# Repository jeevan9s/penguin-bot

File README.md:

# penguin

> <b>P</b>erception-<b>E</b>nabled <b>N</b>avigation and <b>G</b>eneral-<b>U</b>tility <b>IN</b>telligence

Hybrid differential legged-wheeled biped rover for embodied AI, computer vision, and autonomous navigation.

### Status

> - Controller manufactured and partially assembled.
> - Soldering and hardware validation in progress.
> - Mechanical components currently being printed.

<details>`
<summary><strong>Table of Contents</strong></summary>

- [penguin](#penguin)
    - [Status](#status)
  - [Overview](#overview)
  - [Features](#features)
    - [Controller](#controller)
    - [Mechanical](#mechanical)
  - [Architecture](#architecture)
    - [Systems](#systems)
  - [Electrical](#electrical)
    - [Power System](#power-system)
    - [Microcontroller](#microcontroller)
    - [Motor Drivers](#motor-drivers)
    - [Vision Interface](#vision-interface)
    - [Sensor and I2C Interface](#sensor-and-i2c-interface)
    - [Bugs](#bugs)
  - [Mechanical](#mechanical-1)
    - [Chassis](#chassis)
    - [Leg Assembly](#leg-assembly)
  - [Firmware](#firmware)
    - [Architecture](#architecture-1)
    - [Drivers](#drivers)
    - [Engine](#engine)
      - [State \& System Definitions](#state--system-definitions)
      - [Controllers \& Locomotion](#controllers--locomotion)
      - [Behaviour](#behaviour)
    - [Networking](#networking)
    - [GUI](#gui)
  - [Gallery](#gallery)

</details>

I built penguin cause I wanted to create an intelligent robot from the ground up.

<table>
  <tr>
    <td width="50%">
      
    </td>
    <td width="50%">
      
    </td>
  </tr>
  <tr>
    <td width="50%">
      
    </td>
    <td width="50%">
      
    </td>
  </tr>
    <tr>
    <td width="50%">
      
    </td>
    <td width="50%">
      
    </td>
  </tr>
</table>

## Overview

Put simply, Penguin is a platform for experimentation with intelligent robotics.

The project began as a simpler, maze-solving rover for a course project (MREN 178 - DSA). My team couldn't deliver the rover in time
so we scaled down. I had already started with hardware, which pushed me to adopt the project into my own, with the intent to expand it past maze-solving.

After that term (Winter '26), I designed a controller PCB and the necessary compoments for the chassis.

Now its September, and I'm tuning PID.

## Features

### Controller

The controller is powered by a 7.4V LiPo Battery and driven by an ESP32-S3 (N16 1U).

Below is a list of features from power circuits to various peripherals.

- Power-entry circuitry with OC/OV protetction, RPP, PI-filter, and dual-mosfet BMS.
- Regulation circuit featuring buck converter, 5V ORing, and LDO for logic power (3V3)
- ESP32-S3 breakout circuitry with USB differential routing, S3 boot mode selection and reset toggle.
- Controlled power delivery via CMOS circuits for main motor power.
- N20 motors with encoders for wheels driven by a DRV8833 chip.
- DS3218 20kg Servo motors for hip joints, driven by PWM signals from S3.
- OV2640 camera with FPC connector and three-level voltage regulation.
- I2C bus with three ToF sensors, OLED screen, and GPIO expander.
- Audible and visual indicators.
- cool silkscreen penguin.

### Mechanical

- Three-layer internal stackup for housing motors, controller board, and routing cables.
- Integrated vents and ports for sensors and devices, air flow, and weight reduction.
- Hybrid locomotion system with wheels and legs.
- Multi-bar leg assembly - pivot arm, mounting arm (hip), leg.

## Architecture

### Systems

## Electrical

This section provides low-level explanations of the significant circuits of each "module" of the controller.

I encourage you to clone the repo or you use [KiCanvas](https://kicanvas.org/) to look at the schematic and board files.

All electronics were designed with **KiCad**.

### Power System

**Power Entry**

The 7.4V battery power enters through a Molex Micro-Fit (3mm Pitch) header, where it is then met with a 12V 7A fuse for over-current protection. A PTC resettable fuse was selected for durability.

The positive battery line is then protected from voltage spikes with a Transient Voltage Supression (TVS) diode placed in paralell for clamping.

- The diode's standoff @ `9V`
- Breakdown @ `10V`
- Clamps @ `15.4V`

The positive line then goes through a Reverse Polarity Protection (RPP) circuit, using a P-Channel MOSFET for lossless efficiency (lower V drop than standard diodes).

A Zener diode and resistor is placed between the MOSFET's gate and source for gate over-voltage protection.

A bulk electrolytic (100μF) capacitor, ferrite bead, and high-frequency (0.1μF) capacitor are then placed to create a third-order low pass filter (π-filter).

- This is used to smooth voltage spikes and reduce EMI.

The ferrite bead was primariy selected for its saturation current and DCR.

The approximate current draw with safety margin $I_{net}$ is 5A.

$I_{\mathrm{sat}} = 1.5 \times I_{\mathrm{net}} \approx 10 A$

Minimize heat dissipation.

$DCR$ is 10Ω

$P_{heat} = DCR \times I_{\mathrm{sat}} \approx 0.25 W$

**Battery-Management-System (BMS)**

The BMS system uses the negative terminal of the battery and features a `HY2120` protection IC with a dual-mosfet to form the system's **GND**.

The IC uses the balance tap of the battery (VC ~ 3.7V nominal) to monitor the level of Cell 1, while using the main positive terminal (VDD ~ 7.4V nominal) to monitor Cell 2.

This allows the IC to indepdently track each cell's voltage and trigger the dual-MOSFET to cut off power if either cell suffers from overcharge or overdischarge.

**Voltage Regulation (I)**

The controller uses a cascade regulation system, starting with the `TPS5405DR` buck converter.

The input voltage is `VBATT` (7.4V), after the protection and filtering circuitry, and the output is 5V.

The $R_{osc}$ value will determine the switching frequency of the converter.

Switching frequency is governed by the relationship.
$$R_{\text{OSC}} (\text{k}\Omega) = 21.82 \cdot f_{\text{SW}}^{-1.167}$$

I chose a value of `100kΩ` for a $f_{SW}$ of approximately `271 kHz`

For the soft-start capacitor $C_{ss}$ , I chose a value of `10nF` for a soft-start time of `5ms`

The values below were taken from the [TPS5405DR Datasheet](https://www.ti.com/lit/gpn/tps5405)

$$
C_{SS} = \frac{t_{SS} \cdot I_{SS}}{V_{REF}}
$$

$$
C_{SS} = \frac{(5\,\mathrm{ms})(2\,\mathrm{\mu A})}{0.8\,\mathrm{V}}
= 12.5\,\mathrm{nF}
\approx 10\,\mathrm{nF}
$$

The inductor values were chosen using the equation below.

$$
L=\frac{V_{out}\left(V_{in}-V_{out}\right)}
{V_{in}f_{sw}\Delta I_L}
$$

Using our calculated $f_{sw}$ from above and our voltage requirements (8.4V in, 5V out):

$$
L=
\frac{(5\,\mathrm{V})(8.4\,\mathrm{V}-5\,\mathrm{V})}
{(8.4\,\mathrm{V})(525\,\mathrm{kHz})(0.3\,\mathrm{A})}

\approx
10\,\mathrm{\mu H}
$$

The Schottky diode is rated for the `2A` output current and `8.4V`

**5V ORing**

The `5V` rails from both USB and the buck converter are combined using an OR-ing circuit (Dual Ideal Diodes) to prevent backfeeding before feeding the second stage of regulation.

In this configuration, the outputs of both `LM66100` ideal diode controllers are tied together to form the shared `5V` rail. The `CE` pins of each device are also tied to the output rail, ensuring both controllers are only enabled once the rail is present

**Voltage Regulation (II)**

The second stage of voltage regulation involes a Low-Dropout Regulator (LDO), the `AMS1117`

It is fed the combined `5V` rail from the OR-ing circuit to produce the controller's logic-level voltage: `3V3`

**Controlled Motor Power Delivery**

The power for the N20 and Servo motors is controlled using a complementary-MOSFET (CMOS) setup, driven by a digital `HIGH` from the S3.

- When the control signal is low or floating, the N-channel MOSFET remains off and a pull-up resistor holds the gate of the P-channel MOSFET at the supply voltage, keeping it disabled and disconnecting the load rail.

- When the control signal is driven high, the N-channel MOSFET turns on and pulls the P-channel gate low, creating sufficient gate-source voltage to enable conduction and connect the supply to the load.

This controlled power line, `VMOT = 7.4V` powers the supply voltage of the `DRV8833` chip, and is converted via local buck converter to produce `VSERVO = 5V`

**Voltage Sensing**

A resistor divider circuit is used to produce a signal to be read by the S3's internal ADC.

- $R_1 = 100\,\mathrm{k\Omega}$
- $V_{batt} = 7.4\,\mathrm{V}$
- $V_{out} = 2.8\,\mathrm{V}$

$$
R_2 = \frac{R_1 \cdot V_{out}}{V_{batt} - V_{out}}
$$

$$
R_2 = \frac{100\,000 \cdot 2.8}{7.4 - 2.8}
= 50\,\mathrm{k\Omega}
\approx 47\,\mathrm{k\Omega}
$$

### Microcontroller

The controller is driven by an ESP32-S3-WROOM-1U-N16 microcontroller.

The `U` and `N16` model was selected for layout flexibility and memory capacity (16MB).

A `MCP23017` GPIO expander was used to accomodate space for all digital inputs/outputs (via `I2C`)

**Digital IO**

**Mode Select and Reset Toggle**

The S3 can be put into **BOOT** mode and **RESET** with onboard buttons.

**BOOT** mode determines whether the chip runs existing code from flash memory or waits to download new firmware.

- The ESP32 samples the **BOOT** pin (`GPIO0`) during reset to determine the boot mode.
- It is **active-low**: when pulled to **GND** during reset, the chip enters UART bootloader mode for flashing firmware.
- The circuit uses a momentary push-button to **GND** and a `10kΩ` pull-up resistor to ensure a defined high state during normal operation.

| BOOT0 Level | Boot Mode        |
| ----------- | ---------------- |
| HIGH        | Programming Mode |
| LOW         | Memory Mode      |

**RESET** controls the Enable (EN) pin which is the ON/OFF (reset) switch for the ESP32.

- It is **active-low**: when pulled to **GND** it turns off the chip, and when released, it restarts.
- The circuit consists of a momentary push-button, a pull-up resistor to ensure the chip is enabled by default, and a `1µF` capacitor to filter out button noise.

### Motor Drivers

The `N20` wheel hub motors are driven by a `DRV8833` chip, and their encoder signals are routed to digital pins on the `S3`.

They are connected via 6-Pin Molex Nano-Fit (2.50mm Pitch) headers, and feature decoupling across the motor terminals and on the encoder power supply.

The **Servo** hip motors are driven by PWM signals from the `S3`, and are connected by a single 4-Pin Molex Nano-Fit header.

The connector has decoupling on the power supply, and series resistors on the signal lines to improve signal integrity and reduce noise.

### Vision Interface

The controller interfaces with an `OV2640` camera via FPC-connector.

The camera is configured in **8-bit** mode using adjacent digital pins for frames.

Power supply is divided into three levels:

- `DVDD`: **1.2V**
- `AVDD`: **2.8V**
- `DOVDD`: **3.3V**

These conversions are acheived through the use of fixed-output-voltage LDOs (`LP5907MFX`) with local decoupling.

Series low-resistance resistors were added on the camera's clock signals (PCLK, XCLK) in series for signal integrity and EMI reduction.

- I used only `S3` pins, not expander pins, for the data pins `D2-D9` and `HREF`, `VSYNC` pins.

### Sensor and I2C Interface

The controller interfaces with three `VL53L0X` Time-of-Flight (ToF) sensors for ranging (obstacle detection, SLAM - potentially).

This interface is achieved through `I2C`.

The sensors are connected through a single 7-Pin Molex Nano-Fit header, connecting the sensor power, I2C clock and data signals, and the shutdown `XSHUT` pins of each sensor.

Decoupling capacitors and shutdown pull-ups are placed locally.

**Additional I2C Devices**

- IMU (LSM6DSL)
- Mini OLED Screen
- OV2640 Cam

**Indicator Components**

- RGB LED
- Passive LEDs for simple indication
- Buzzer for audible indication

### Bugs

- Misoriented cam header -- fixed with an extenison board + B-Type FPC cable
- DRV8833 VM and VINT pins missing GND connection
- Buzzer and RGB LED pins need clock signal but wired to MCP pins.

## Mechanical

This section provides insight on the mechanical components of Penguin: the chassis and leg assembly.

In no way am I a CAD-expert, so this was definitely a learning experience with lots of iteration.

Projected geomtery was clutch.

I used Fusion360 to design everything.

### Chassis

The chassis consists of several components attatched with pegs and magnets.

**Base Plate**

The base plate forms the start of the internal stack-up.

It contains Servo pads for the hip motors to rest on, a port for an ON/OFF switch, and a battery slot with vents.

It acts as the "floor" of the Servo bay and the bottom of the chassis.

It connects to the rest of the chassis through pegs to insert into the inside face of each wall, as well as the nose.

**Side Walls**

<table><tr><td width="50%"></td><td width="50%"></td></tr></table>

The side-walls enclose the internal stack-up, and provide mounting points for several chassis components.

Mounting tabs are on the inside of each wall for board mounting.

They have cutouts for the Servo shafts, arm joints, and house components like the external antenna.
The top face has short holes for magnets that align with holes on the lid.

**Nose**

The nose contains ports for the ToF sensors, and an OLED screen.

There is also an open face cable port connecting to the controller bay for routing.

It mounts to each walls with pegs and magnets, as well as to the base plate.

**Stern**

The stern features a USB-port and snaps to the walls via pegs.

**Lid**

The lid contains a magnet cutouts for mounting the camera mount, and is magnetically mounted on the top surface of the walls and nose.

**Camera Mount**

The mount features a porthole for the OV2640 camera lens, and corresponding magnet cutouts for mating with the roof.

### Leg Assembly

The leg assembly consists of the Servo mounting arm, pivot arm, and the wheel hub assembly.

**Mounting Arm**

This is the contact point between the leg assembly and the hip motor, it's responsible for driving the assembly.

The Servo uses the disc-horn, and fits into a cutout on the mounting arm, and is secured in with the stock machine screw into the shaft.

The end of the arm mounts onto the wheel hub assembly using bearings on each hole, an M3 shoulder bolt, and a nut.

**Pivot Arm**

The pivot arm maintains proper orientation for the assembly as the suspension moves up and down.

It uses the same mounting as the mounting arm (bearing, shoulder bolt, nut), and is mounted slightly higher at a 40° angle on the wheel hub assembly.

**Wheel Hub Assembly**

This component houses the N20 motors through a cutout and U-Channel cover to secure them.

The top of the assembly contains the two mounting points for the pivot and mounting arms.

Cables are routed up the back side of it.

## Firmware

Firmware was written in `C++` using the `Arduino` framework via `PlatformIO`.

All implementations can be found in the [`firmware/src`](firmware/src) directory.

### Architecture

The firmware design is divided into three distinct layers:

- **HAL Drivers**
  - Abstraction of interfaces with hardware components.
- **Core Engine**
  - Controllers and state definitions
- **Networking**
  - Telemetry for GUI

### Drivers

Hardware drivers are used to abstract hardware interfaces for motors and sensors.

Each driver exports a class that follows a consistent structure:

```cpp
class Driver {
  public:
    Driver(uint8_t pin);
    bool begin();
    Data read(); // return type unique to hardware
    void run();
};
```

Sensory drivers such as ToFs, IMU, and camera export reads.

Actuator drivers export runs, but the DC motor driver exports a read for the encoders.

In terms of integration, drivers are instantiated at the application level (main.cpp), and are invoked by the scheduler for telemetry, and by the locomotion engine for motor control.

### Engine

The engine layer encapsulates all state machine, control, and behavioural logic into several classes.

- State & System Definitions
  - Data types, schema for global data instance
- Controllers and Locomotion
  - PID utility class, motor control
- Behaviour
  - Motion primitives and routines

#### State & System Definitions

This section defines shapes for all system objects, including IMU, ToF, and motor data.

<details>
<summary>IMU Data Object</summary>

```cpp

struct IMUData
{
  float accX; // g
  float accY;
  float accZ;

  float gyX; // dps
  float gyY;
  float gyZ;

  float temp; // C

  Rotation angles;
};

```

</details>

This and other data types are placed in a `PenguinState` struct which acts as the global state for telemetry lookup and velocity controllers. 

Additionally, it implements a `PenguinCommands` field, which is observed by locomotion controllers and updated by mmotion primitives. 
- Commands specify desired pitch, RPM, and hip angles. 

#### Controllers & Locomotion
The locomotion layer manages the low-level **movement** of the robot. 

It is blind to routines; it doesn't know *when* to move but it knows how to adjust its motion given a command (orchestrated autonomously by the Behaviour layer). 

A utility PID class is used as the basis for locomotion controller. 

It calculates an error value as the difference between a target setpoint and a mesaured proces variable, then applies a correction based on proportional, integral, and derivative terms, to smoothly drive the controller toward its desired state. 

$$u(t) = K_p e(t) + K_i \int_{0}^{t} e(\tau) d\tau + K_d \frac{de(t)}{dt}$$

The layer defines two important controllers: 
- **Balance Controller**
  - Produces an optimal RPM based on a target pitch. 
  - Uses the IMU pitch rate as derivative term in the PID Equation. 

- **Velocity Controller**
  - Produces an optimal PWM based on a target RPM. 
  - Target RPM is split into differential-drive inputs to be fed into two distinct controllers (L, R). 
    - $$v_{\text{lr}} = v_{\text{fwd}} - v_{\text{turn}} + v_{\text{corr}}$$

The main Locomotion engine then wraps these controllers within an update method to observe the `RobotCommands` struct and adjusts accordingly. 
- Hip motors are also driven here for stance adjustment. 

#### Behaviour
The behaviour layer defines the buidling blocks of Penguin's movement: 
- Motion Primitives
  - Movement actions. 
- Routines
  - Sequences of motion primitives. 

Primitives directly update `RobotCommands`, and form key positions and stances. 

Routines are simply **sequences** of motion primitives, and are tracked using a step-counter and a non-blocking timer. 
- Transitions are smoothed using **Linear Interpolation**

The routine class exports an `update` method for switching between different routines. 

This method is used in the `Behaviour` implementation. 
- Currently it autonomously runs a default cycling routine with obstacle avoidance using the ToF sensors and reverse primitives. 

### Networking
This layer leverages an asynchronous HTTP server and Websockets for streaming data to the GUI. 

The `ESPAsyncWebServer.h` is wrapped in a class `HTTPServer` which implements `begin` and `update` methods which initializes the Websocket connection, and sends the telemetry packet. 

The firmware data packet is serialized into a JsonDocument before streaming. 

The telemetry packet contains:
- Motor Data 
  - RPM, position, running boolean
- IMU Data 
  - Pitch, roll, yaw, three-axis acceleration
- ToF Data (For each sensor)
  - Proximity in mm
  - Obstacle Detection boolean
- Battery Data
  - SOC
  - Connected boolean

The payload updates are orchestrated by the **Scheduler**

| Component | Update Frequency | Update Period (Interval) |
| :--- | :--- | :--- |
| **IMU** | 100 Hz | 10 ms |
| **Motors** | 50 Hz | 20 ms |
| **TOF Sensors** | 25 Hz | 40 ms |
| **Battery Data** | 2 Hz | 500 ms |

The live camera feed is streamed **directly** over HTTP. 

**Camera Stream**

The camera driver captures frames as JPEG images and exposes them through the controller's HTTP server at:

```text
http://<controller-ip>/stream
```

The endpoint uses a `multipart/x-mixed-replace` response with a `frame` boundary, allowing a browser to display the feed directly as an MJPEG stream. The dashboard uses this endpoint as the source of an `` element, so no additional decoding or polling loop is required on the client.

The current capture configuration is:

- `VGA` frame size (`640 x 480`)
- JPEG pixel format
- JPEG quality setting of `10`
- Two frame buffers using `CAMERA_GRAB_LATEST`
- Approximately `30 ms` delay between released frames to limit stream pressure

Each request owns its stream state and releases the camera frame buffer when the frame has been sent or the client disconnects. The camera must be initialized before the HTTP server is used; the root endpoint at `http://<controller-ip>/` returns `penguin --online` as a simple connectivity check.

### GUI
The dashboard (GUI) is developed in Next.js and is ran as a local web-app. 

It displays:
- A frame view of the live camera feed.
- Three.js & IMU driven board visualization
- Proximity data visuals 
- Spedometer view for motor data

The app simply listens to the streamed Websocket, extracts the payload, and populates the according data objects.

## Gallery

---
Jeevan Sanchez, 2026

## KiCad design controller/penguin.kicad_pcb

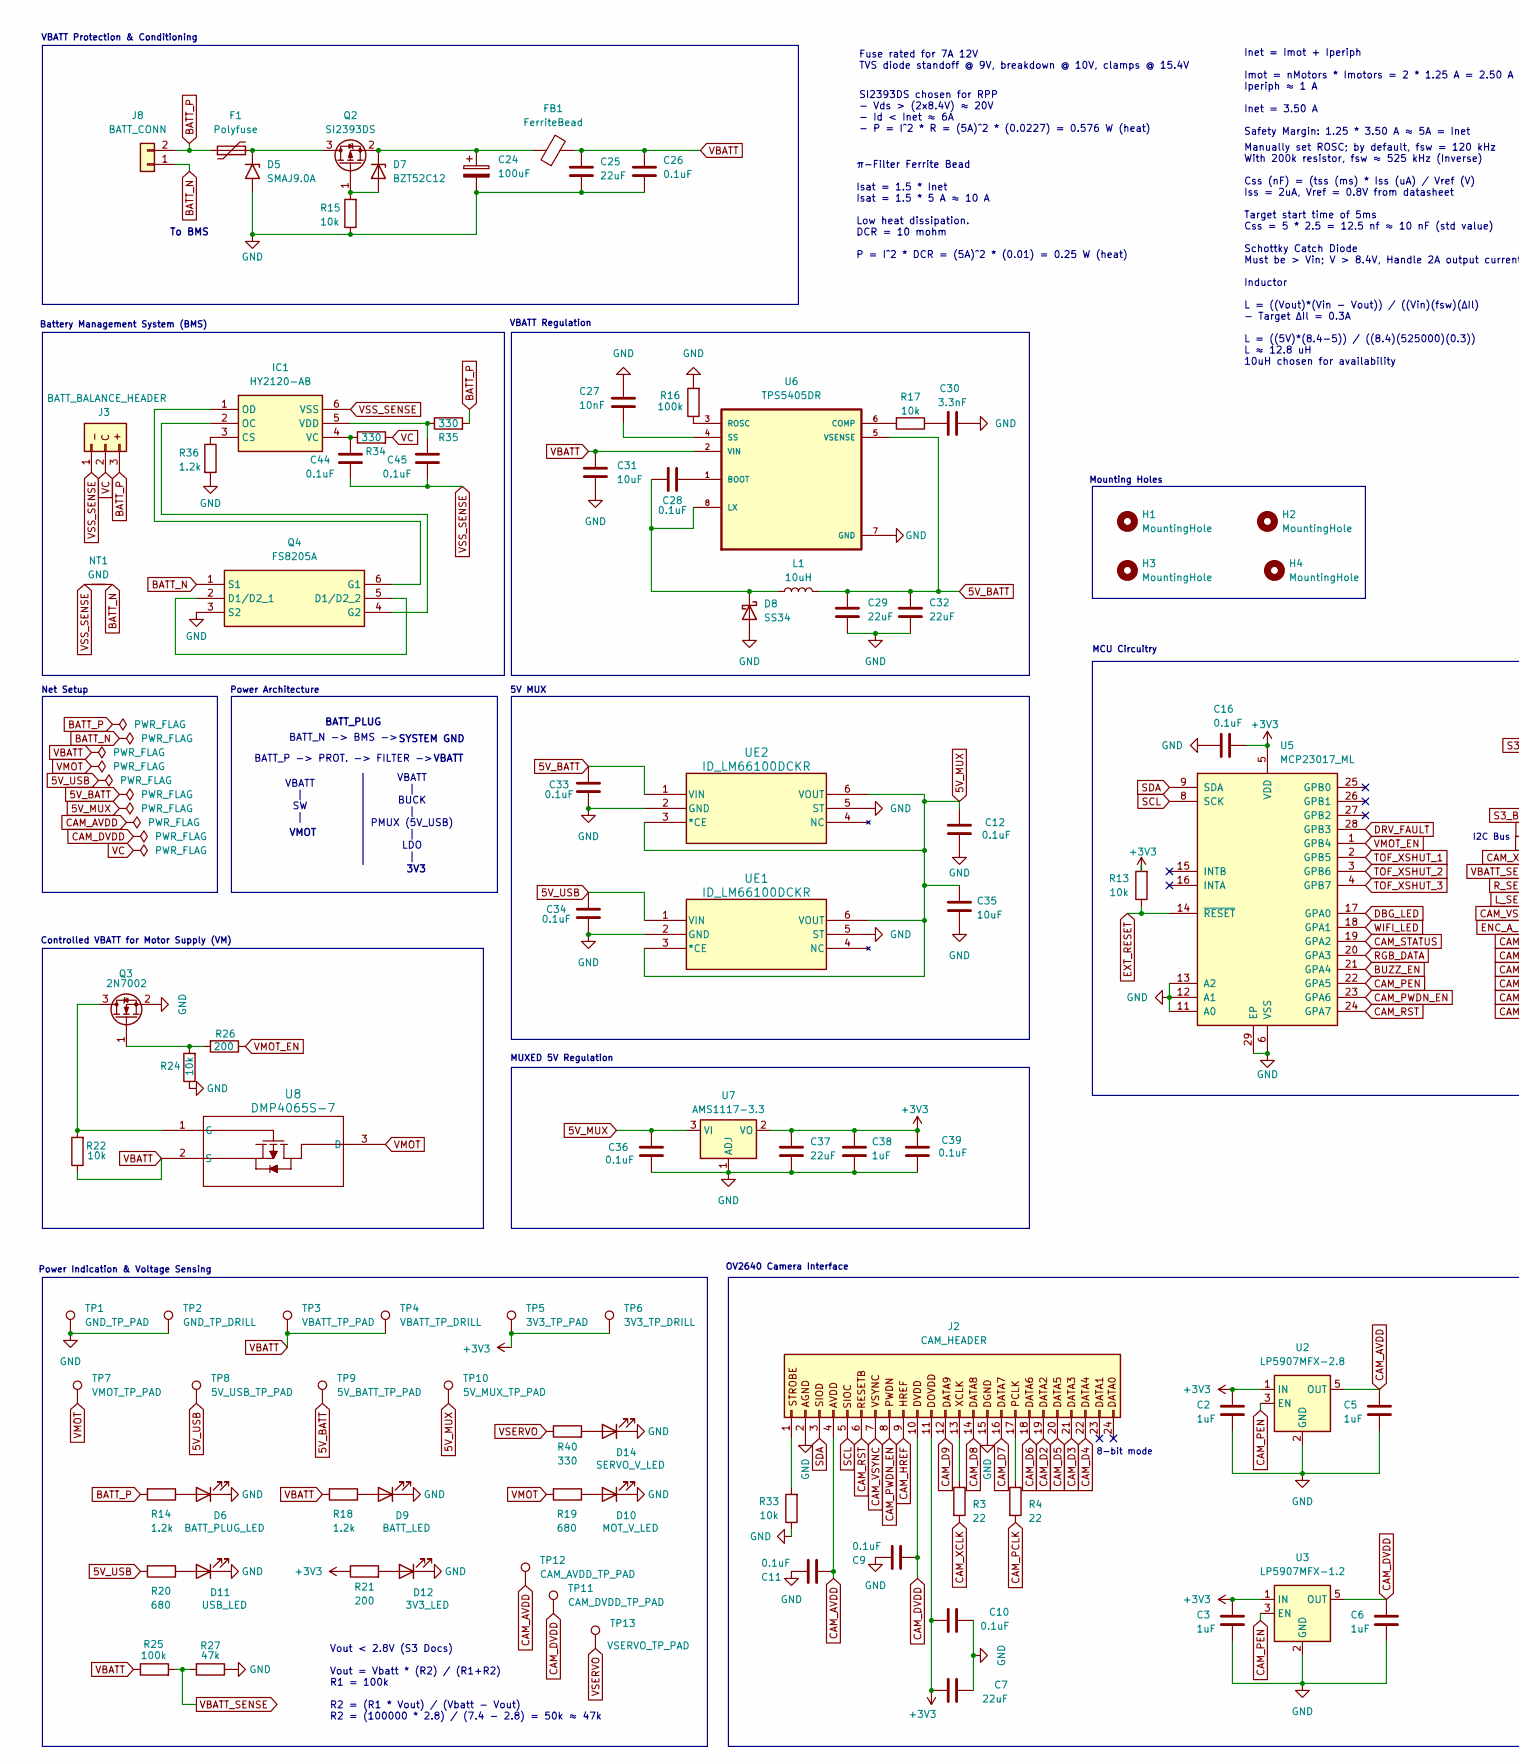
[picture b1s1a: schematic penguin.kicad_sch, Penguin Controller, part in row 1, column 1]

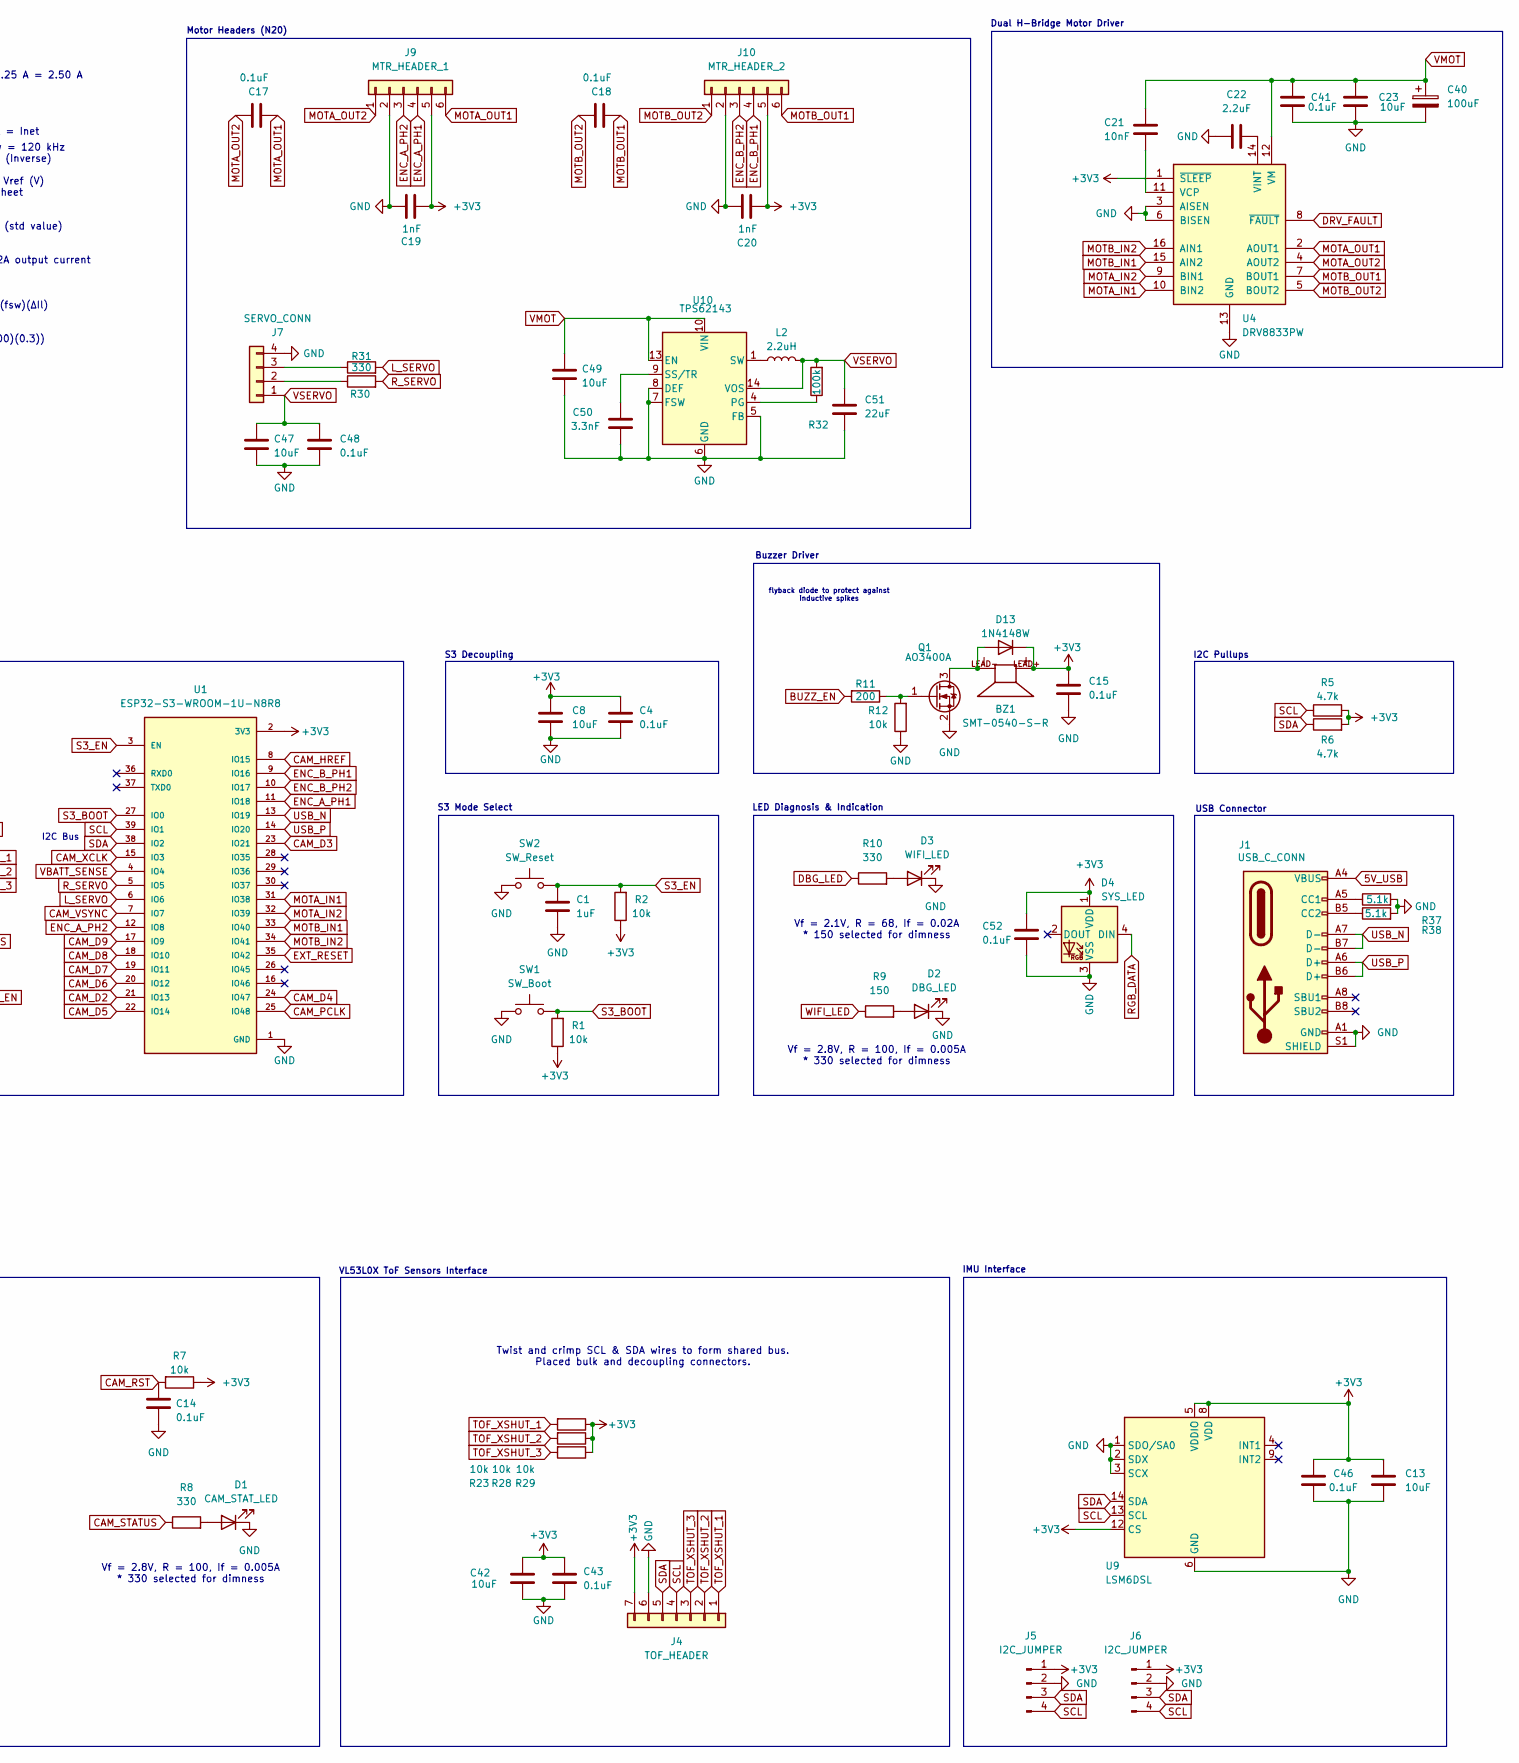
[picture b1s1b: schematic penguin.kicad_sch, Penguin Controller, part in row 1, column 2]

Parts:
BZ1: SMT-0540-S-R; XDCR_SMT-0540-S-R; PARTREV D
C1: 1uF; C_0402_1005Metric; LCSC C52923
C2, C3, C5, C6, C38: 1uF; C_0603_1608Metric; LCSC C15849
C4, C10, C12, C14, C17, C18, C28, C33, C34, C36, C39, C41, C43, C44, C45, C46: 0.1uF; C_0603_1608Metric; LCSC C14663
C7, C25: 22uF; C_0805_2012Metric; LCSC C29277
C8, C13, C23, C31, C35, C42, C47, C49: 10uF; C_0805_2012Metric; LCSC C15850
C9, C11, C15, C16, C48, C52: 0.1uF; C_0402_1005Metric; LCSC C1581
C19, C20: 1nF; C_0603_1608Metric; LCSC C1588
C21: 10nF; C_0402_1005Metric; LCSC C15195
C22: 2.2uF; C_0402_1005Metric; LCSC C12530
C24, C40: 100uF; CAP_EEEFK1V101P; Digikey ZK1V101XV
C26: 0.1uF; C_0805_2012Metric; LCSC C49678
C27: 10nF; C_0603_1608Metric; LCSC C15195
C29, C32, C37, C51: 22uF; C_1206_3216Metric; LCSC C49326779
C30, C50: 3.3nF; C_0402_1005Metric; LCSC C1536
D1: CAM_STAT_LED; LED_0603_1608Metric; LCSC C2290
D2: DBG_LED; LED_0603_1608Metric; LCSC C72038
D3: WIFI_LED; LED_0603_1608Metric; LCSC C72041
D4: SYS_LED; LED_WS2812B-Mini_PLCC4_3.5x3.5mm; Digikey 1568-COM-16347CT-ND
D5: SMAJ9.0A; D_SMA; Digikey SMAJ9.0ABTR-ND
D6: BATT_PLUG_LED; LED_0805_2012Metric; LCSC C2297
D7: BZT52C12; D_SOD-323; LCSC BZT52C12
D8: SS34; D_SMA; LCSC C8678
D9: BATT_LED; LED_0805_2012Metric; LCSC C2297
D10: MOT_V_LED; LED_0603_1608Metric; LCSC C2289
D11: USB_LED; LED_0805_2012Metric; LCSC C2297
D12: 3V3_LED; LED_0805_2012Metric; LCSC C2297
D13: 1N4148W; D_SOD-123; LCSC C81598
D14: SERVO_V_LED; LED_0603_1608Metric; LCSC C2289
F1: Polyfuse; Fuse_1210_3225Metric_Pad1.42x2.65mm_HandSolder; Digikey F8137TR-ND
FB1: FerriteBead; R_0805_2012Metric; LCSC C136227
H1, H2, H3, H4: MountingHole; MountingHole_2.2mm_M2
IC1: HY2120-AB; SOT95P280X140-6N; LCSC C116509
J1: USB_C_CONN; USB_C_Receptacle_G-Switch_GT-USB-7010ASV; LCSC C5178541
J2: CAM_HEADER; Hirose_FH12-24S-0.5SH_1x24-1MP_P0.50mm_Horizontal; LCSC C202112
J3: BATT_BALANCE_HEADER; CONN_SD-105313-100_03_MOL; Digikey WM14973-ND
J4: TOF_HEADER; CONN_SD-105313-100_07_MOL; Digikey WM16898-ND
J5, J6: I2C_JUMPER; PinHeader_1x04_P1.27mm_Vertical; LCSC C6333215
J7: SERVO_CONN; CONN_SD-105313-100_04_MOL; DigiKey WM14974-ND
J8: BATT_CONN; MOLEX_436500204; Digikey WM1875-ND
J9: MTR_HEADER_1; CONN_SD-105313-100_06_MOL; Digikey WM16893-ND
J10: MTR_HEADER_2; CONN_SD-105313-100_06_MOL; Digikey WM16893-ND
L1: 10uH; IND_IFSC_1515AH_VIS; LCSC C187450
L2: 2.2uH; L_Wurth_WE-LQSH-4020; LCSC C5521727
NT1: GND; NetTie-2_SMD_Pad0.5mm
Q1: AO3400A; SOT-23; LCSC C20917
Q2: SI2393DS; SOT-23; LCSC C41348109
Q3: 2N7002; SOT-23; LCSC C8545
Q4: FS8205A; SOT95P280X125-6N; LCSC C908265
R1, R2, R7, R12, R13, R17, R23, R28, R29, R33: 10k; R_0402_1005Metric; LCSC C25744
R3, R4: 22; C_0402_1005Metric; LCSC C25092
R5, R6: 4.7k; R_0402_1005Metric; LCSC C25900
R8, R10, R30, R31, R34, R35, R40: 330; R_0402_1005Metric; LCSC C25104
R9: 150; R_0402_1005Metric; LCSC C72038
R11: 200; R_0402_1005Metric; LCSC C25087
R14, R18, R36: 1.2k; R_0603_1608Metric; LCSC C22765
R15, R22, R24: 10k; R_0603_1608Metric; LCSC C25804
R16, R25, R32: 100k; R_0603_1608Metric; LCSC C25803
R19, R20: 680; R_0603_1608Metric; LCSC C23228
R21, R26: 200; R_0603_1608Metric; LCSC C8218
R27: 47k; R_0603_1608Metric; LCSC C25819
R37, R38: 5.1k; R_0603_1608Metric; LCSC C23186
SW1: SW_Boot; SW_5-B-B-B-A_XKB; LCSC C561514
SW2: SW_Reset; SW_5-B-B-B-A_XKB; LCSC C561514
TP1: GND_TP_PAD; TestPoint_Pad_1.5x1.5mm
TP2: GND_TP_DRILL; TestPoint_THTPad_D1.0mm_Drill0.5mm
TP3: VBATT_TP_PAD; TestPoint_Pad_1.5x1.5mm
TP4: VBATT_TP_DRILL; TestPoint_THTPad_D1.0mm_Drill0.5mm
TP5: 3V3_TP_PAD; TestPoint_Pad_1.5x1.5mm
TP6: 3V3_TP_DRILL; TestPoint_THTPad_D1.0mm_Drill0.5mm
TP7: VMOT_TP_PAD; TestPoint_Pad_1.0x1.0mm
TP8: 5V_USB_TP_PAD; TestPoint_Pad_1.0x1.0mm
TP9: 5V_BATT_TP_PAD; TestPoint_Pad_1.0x1.0mm
TP10: 5V_MUX_TP_PAD; TestPoint_Pad_1.0x1.0mm
TP11: CAM_DVDD_TP_PAD; TestPoint_Pad_1.0x1.0mm
TP12: CAM_AVDD_TP_PAD; TestPoint_Pad_1.0x1.0mm
TP13: VSERVO_TP_PAD; TestPoint_Pad_1.0x1.0mm
U1: ESP32-S3-WROOM-1U-N8R8; ESP32-S3-WROOM-1U; LCSC C2980300
U2: LP5907MFX-2.8; SOT-23-5; LCSC C186700
U3: LP5907MFX-1.2; SOT-23-5; LCSC C73478
U4: DRV8833PW; TSSOP-16_4.4x5mm_P0.65mm; LCSC C544801
U5: MCP23017_ML; QFN-28-1EP_6x6mm_P0.65mm_EP4.25x4.25mm; LCSC C629439
U6: TPS5405DR; SOIC127P599X175-8N; LCSC C488409
U7: AMS1117-3.3; SOT-223-3_TabPin2; LCSC C6186
U8: DMP4065S-7; SOT-23; LCSC C182476
U9: LSM6DSL; LGA-14_3x2.5mm_P0.5mm_LayoutBorder3x4y; LCSC C94048
U10: TPS62143; VQFN-16-1EP_3x3mm_P0.5mm_EP1.68x1.68mm_ThermalVias; LCSC C140242
UE1, UE2: ID_LM66100DCKR; SOT-363_SC-70-6; LCSC C2869734

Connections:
5V_BATT: C29.1, C32.1, C33.2, L1.2, TP9.1, U6.5 (VSENSE), UE2.1 (VIN)
5V_MUX: C12.2, C35.2, C36.2, TP10.1, U7.3 (VI), UE1.3 (*CE), UE1.6 (VOUT), UE2.3 (*CE), UE2.6 (VOUT)
5V_USB: C34.1, J1.A4 (VBUS), J1.A9 (VBUS), J1.B4 (VBUS), J1.B9 (VBUS), R20.2, TP8.1, UE1.1 (VIN)
+3V3: BZ1.LEAD+, C2.1, C3.1, C4.1, C7.1, C8.1, C10.1, C13.1, C15.1, C16.1, C19.2, C20.2, C37.1, C38.1, C39.2, C42.1, C43.1, C46.2, C52.1, D4.1 (VDD), D13.1 (K), J2.11, J4.7, J5.1, J6.1, J9.5, J10.5, R1.1, R2.1, R5.2, R6.2, R7.1, R13.2, R21.1, R23.1, R28.1, R29.1, TP5.1, TP6.1, U1.2 (3V3), U2.1 (IN), U3.1 (IN), U4.1 (~SLEEP), U5.5 (VDD), U7.2 (VO), U9.5 (VDDIO), U9.8 (VDD), U9.12 (CS)
BATT_N: J8.1, NT1.2, Q4.1 (S1)
BATT_P: F1.1, J3.3, J8.2, R14.2, R35.2
BUZZ_EN: R11.2, U5.21 (GPA4)
CAM_AVDD: C5.1, C11.1, J2.4, TP12.1, U2.5 (OUT)
CAM_D2: J2.19, U1.21 (IO13)
CAM_D3: J2.21, U1.23 (IO21)
CAM_D4: J2.22, U1.24 (IO47)
CAM_D5: J2.20, U1.22 (IO14)
CAM_D6: J2.18, U1.20 (IO12)
CAM_D7: J2.16, U1.19 (IO11)
CAM_D8: J2.14, U1.18 (IO10)
CAM_D9: J2.12, U1.17 (IO9)
CAM_DVDD: C6.1, C9.1, J2.10, TP11.1, U3.5 (OUT)
CAM_HREF: J2.9, U1.8 (IO15)
CAM_PCLK: R4.2, U1.25 (IO48)
CAM_PEN: U2.3 (EN), U3.3 (EN), U5.22 (GPA5)
CAM_PWDN_EN: J2.8, U5.23 (GPA6)
CAM_RST: C14.1, J2.6, R7.2, U5.24 (GPA7)
CAM_STATUS: R8.1, U5.19 (GPA2)
CAM_VSYNC: J2.7, U1.7 (IO7)
CAM_XCLK: R3.2, U1.15 (IO3)
DBG_LED: R10.1, U5.17 (GPA0)
DRV_FAULT: U4.8 (~FAULT), U5.28 (GPB3)
ENC_A_PH1: J9.4, U1.11 (IO18)
ENC_A_PH2: J9.3, U1.12 (IO8)
ENC_B_PH1: J10.4, U1.9 (IO16)
ENC_B_PH2: J10.3, U1.10 (IO17)
EXT_RESET: R13.1, U1.35 (IO42), U5.14 (~RESET)
GND: C1.2, C2.2, C3.2, C4.2, C5.2, C6.2, C7.2, C8.2, C9.2, C10.2, C11.2, C12.1, C13.2, C14.2, C15.2, C16.2, C19.1, C20.1, C22.1, C23.2, C24.2, C25.2, C26.2, C27.1, C29.2, C30.2, C31.2, C32.2, C33.1, C34.2, C35.1, C36.1, C37.2, C38.2, C39.1, C40.2, C41.1, C42.2, C43.2, C46.1, C47.1, C48.2, C49.1, C50.1, C51.2, C52.2, D1.1 (K), D2.1 (K), D3.1 (K), D4.3 (VSS), D5.2 (A2), D6.1 (K), D8.2 (A), D9.1 (K), D10.1 (K), D11.1 (K), D12.1 (K), D14.1 (K), J1.A1 (GND), J1.A12 (GND), J1.B1 (GND), J1.B12 (GND), J1.S1 (SHIELD), J2.2, J2.15, J4.6, J5.2, J6.2, J7.4, J9.2, J10.2, Q1.2 (S), Q3.2 (S), Q4.3 (S2), R12.1, R15.1, R16.2, R24.1, R27.1, R33.1, R36.2, R37.2, R38.2, SW1.1, SW2.1, TP1.1, TP2.1, U1.1 (GND), U1.40 (GND), U1.41_1 (GND), U1.41_2 (GND), U1.41_3 (GND), U1.41_4 (GND), U1.41_5 (GND), U1.41_6 (GND), U1.41_7 (GND), U1.41_8 (GND), U1.41_9 (GND), U2.2 (GND), U3.2 (GND), U4.3 (AISEN), U4.6 (BISEN), U4.13 (GND), U5.6 (VSS), U5.11 (A0), U5.12 (A1), U5.13 (A2), U5.29 (EP), U6.7 (GND), U7.1 (ADJ), U9.1 (SDO/SA0), U9.2 (SDX), U9.3 (SCX), U9.6 (GND), U9.7 (GND), U10.5 (FB), U10.6 (GND), U10.7 (FSW), U10.8 (DEF), U10.15 (GND), U10.16 (GND), U10.17 (GND), UE1.2 (GND), UE1.5 (ST), UE2.2 (GND), UE2.5 (ST)
L_SERVO: R31.2, U1.6 (IO6)
MOTA_IN1: U1.31 (IO38), U4.10 (BIN2)
MOTA_IN2: U1.32 (IO39), U4.9 (BIN1)
MOTA_OUT1: C17.2, J9.6, U4.2 (AOUT1)
MOTA_OUT2: C17.1, J9.1, U4.4 (AOUT2)
MOTB_IN1: U1.33 (IO40), U4.15 (AIN2)
MOTB_IN2: U1.34 (IO41), U4.16 (AIN1)
MOTB_OUT1: C18.2, J10.6, U4.7 (BOUT1)
MOTB_OUT2: C18.1, J10.1, U4.5 (BOUT2)
unnamed: C30.1, R17.1
unnamed: D1.2 (A), R8.2
unnamed: D2.2 (A), R9.2
unnamed: D3.2 (A), R10.2
unnamed: D5.1 (A1), F1.2, Q2.3 (D)
unnamed: D6.2 (A), R14.1
unnamed: D7.2 (A), Q2.1 (G), R15.2
unnamed: C24.1, D7.1 (K), FB1.1, Q2.2 (S)
unnamed: C28.1, D8.1 (K), L1.1, U6.8 (LX)
unnamed: D9.2 (A), R18.1
unnamed: D10.2 (A), R19.1
unnamed: D11.2 (A), R20.1
unnamed: D12.2 (A), R21.2
unnamed: BZ1.LEAD-, D13.2 (A), Q1.3 (D)
unnamed: D14.2 (A), R40.2
unnamed: IC1.3 (CS), R36.1
unnamed: IC1.2 (OC), Q4.4 (G2)
unnamed: IC1.1 (OD), Q4.6 (G1)
unnamed: C44.2, IC1.4 (VC), R34.1
unnamed: C45.2, IC1.5 (VDD), R35.1
unnamed: J1.A5 (CC1), R37.1
unnamed: J1.B5 (CC2), R38.1
unnamed: J2.1, R33.2
unnamed: J2.13, R3.1
unnamed: J2.17, R4.1
unnamed: J7.2, R30.1
unnamed: J7.3, R31.1
unnamed: L2.1, U10.1 (SW), U10.2 (SW), U10.3 (SW)
unnamed: Q1.1 (G), R11.1, R12.2
unnamed: Q3.3 (D), R22.2, U8.1 (G)
unnamed: Q3.1 (G), R24.2, R26.2
unnamed: Q4.2 (D1/D2_1), Q4.5 (D1/D2_2)
unnamed: C21.2, U4.11 (VCP)
unnamed: C22.2, U4.14 (VINT)
unnamed: C28.2, U6.1 (BOOT)
unnamed: R17.2, U6.6 (COMP)
unnamed: R16.1, U6.3 (ROSC)
unnamed: C27.2, U6.4 (SS)
unnamed: R32.1, U10.4 (PG)
unnamed: C50.2, U10.9 (SS/TR)
RGB_DATA: D4.4 (DIN), U5.20 (GPA3)
R_SERVO: R30.2, U1.5 (IO5)
S3_BOOT: R1.2, SW1.2, U1.27 (IO0)
S3_EN: C1.1, R2.2, SW2.2, U1.3 (EN)
SCL: J2.5, J4.4, J5.4, J6.4, R5.1, U1.39 (IO1), U5.8 (SCK), U9.13 (SCL)
SDA: J2.3, J4.5, J5.3, J6.3, R6.1, U1.38 (IO2), U5.9 (SDA), U9.14 (SDA)
TOF_XSHUT_1: J4.1, R23.2, U5.2 (GPB5)
TOF_XSHUT_2: J4.2, R28.2, U5.3 (GPB6)
TOF_XSHUT_3: J4.3, R29.2, U5.4 (GPB7)
USB_N: J1.A7 (D-), J1.B7 (D-), U1.13 (IO19)
USB_P: J1.A6 (D+), J1.B6 (D+), U1.14 (IO20)
VBATT: C25.1, C26.1, C31.1, FB1.2, R18.2, R22.1, R25.1, TP3.1, TP4.1, U6.2 (VIN), U8.2 (S)
VBATT_SENSE: R25.2, R27.2, U1.4 (IO4)
VC: J3.2, R34.2
VMOT: C21.1, C23.1, C40.1, C41.2, C49.2, R19.2, TP7.1, U4.12 (VM), U8.3 (D), U10.10 (VIN), U10.11 (VIN), U10.12 (VIN), U10.13 (EN)
VMOT_EN: R26.1, U5.1 (GPB4)
VSERVO: C47.2, C48.1, C51.1, J7.1, L2.2, R32.2, R40.1, TP13.1, U10.14 (VOS)
VSS_SENSE: C44.1, C45.1, IC1.6 (VSS), J3.1, NT1.1
WIFI_LED: R9.1, U5.18 (GPA1)

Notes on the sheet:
VBATT Regulation
Net Setup
Battery Management System (BMS)
Vf = 2.8V, R = 100, If = 0.005A * 330 selected for dimness
Mounting Holes
To BMS
Fuse rated for 7A 12V TVS diode standoff @ 9V, breakdown @ 10V, clamps @ 15.4V
VBATT
S3 Decoupling
I2C Pullups
MCU Circuitry
Vout < 2.8V (S3 Docs) Vout = Vbatt * (R2) / (R1+R2) R1 = 100k R2 = (R1 * Vout) / (Vbatt - Vout) R2 = (100000 * 2.8) / (7.4 - 2.8) = 50k ≈ 47k
Power Indication & Voltage Sensing
BATT_N -> BMS ->
USB Connector
VBATT Protection & Conditioning
Manually set ROSC; by default, fsw = 120 kHz With 200k resistor, fsw ≈ 525 kHz (Inverse) Css (nF) = (tss (ms) * Iss (uA) / Vref (V) Iss = 2uA, Vref = 0.8V from datasheet Target start time of 5ms Css = 5 * 2.5 = 12.5 nf ≈ 10 nF (std value) Schottky Catch Diode Must be > Vin; V > 8.4V, Handle 2A outp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
π-Filter Ferrite Bead Isat = 1.5 * Inet Isat = 1.5 * 5 A ≈ 10 A Low heat dissipation. DCR = 10 mohm P = I^2 * DCR = (5A)^2 * (0.01) = 0.25 W (heat)
Dual H-Bridge Motor Driver
BATT_P -> PROT. -> FILTER ->
Motor Headers (N20)
SI2393DS chosen for RPP - Vds > (2x8.4V) ≈ 20V - Id < Inet ≈ 6A - P = I^2 * R = (5A)^2 * (0.0227) = 0.576 W (heat)
flyback diode to protect against inductive spikes
8-bit mode
5V MUX
VBATT | BUCK | PMUX (5V_USB) | LDO |
Twist and crimp SCL & SDA wires to form shared bus. Placed bulk and decoupling connectors.
MUXED 5V Regulation
IMU Interface
LED Diagnosis & Indication
VMOT
VL53L0X ToF Sensors Interface
Controlled VBATT for Motor Supply (VM)
BATT_PLUG
S3 Mode Select
I2C Bus
Inet = Imot + Iperiph Imot = nMotors * Imotors = 2 * 1.25 A = 2.50 A Iperiph ≈ 1 A Inet = 3.50 A Safety Margin: 1.25 * 3.50 A ≈ 5A = Inet
Vf = 2.1V, R = 68, If = 0.02A * 150 selected for dimness
VBATT | SW |
SYSTEM GND
